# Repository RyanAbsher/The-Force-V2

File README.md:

# The Force V2
 Second version of a show crontroller for The Force Exhibit at the USSRC

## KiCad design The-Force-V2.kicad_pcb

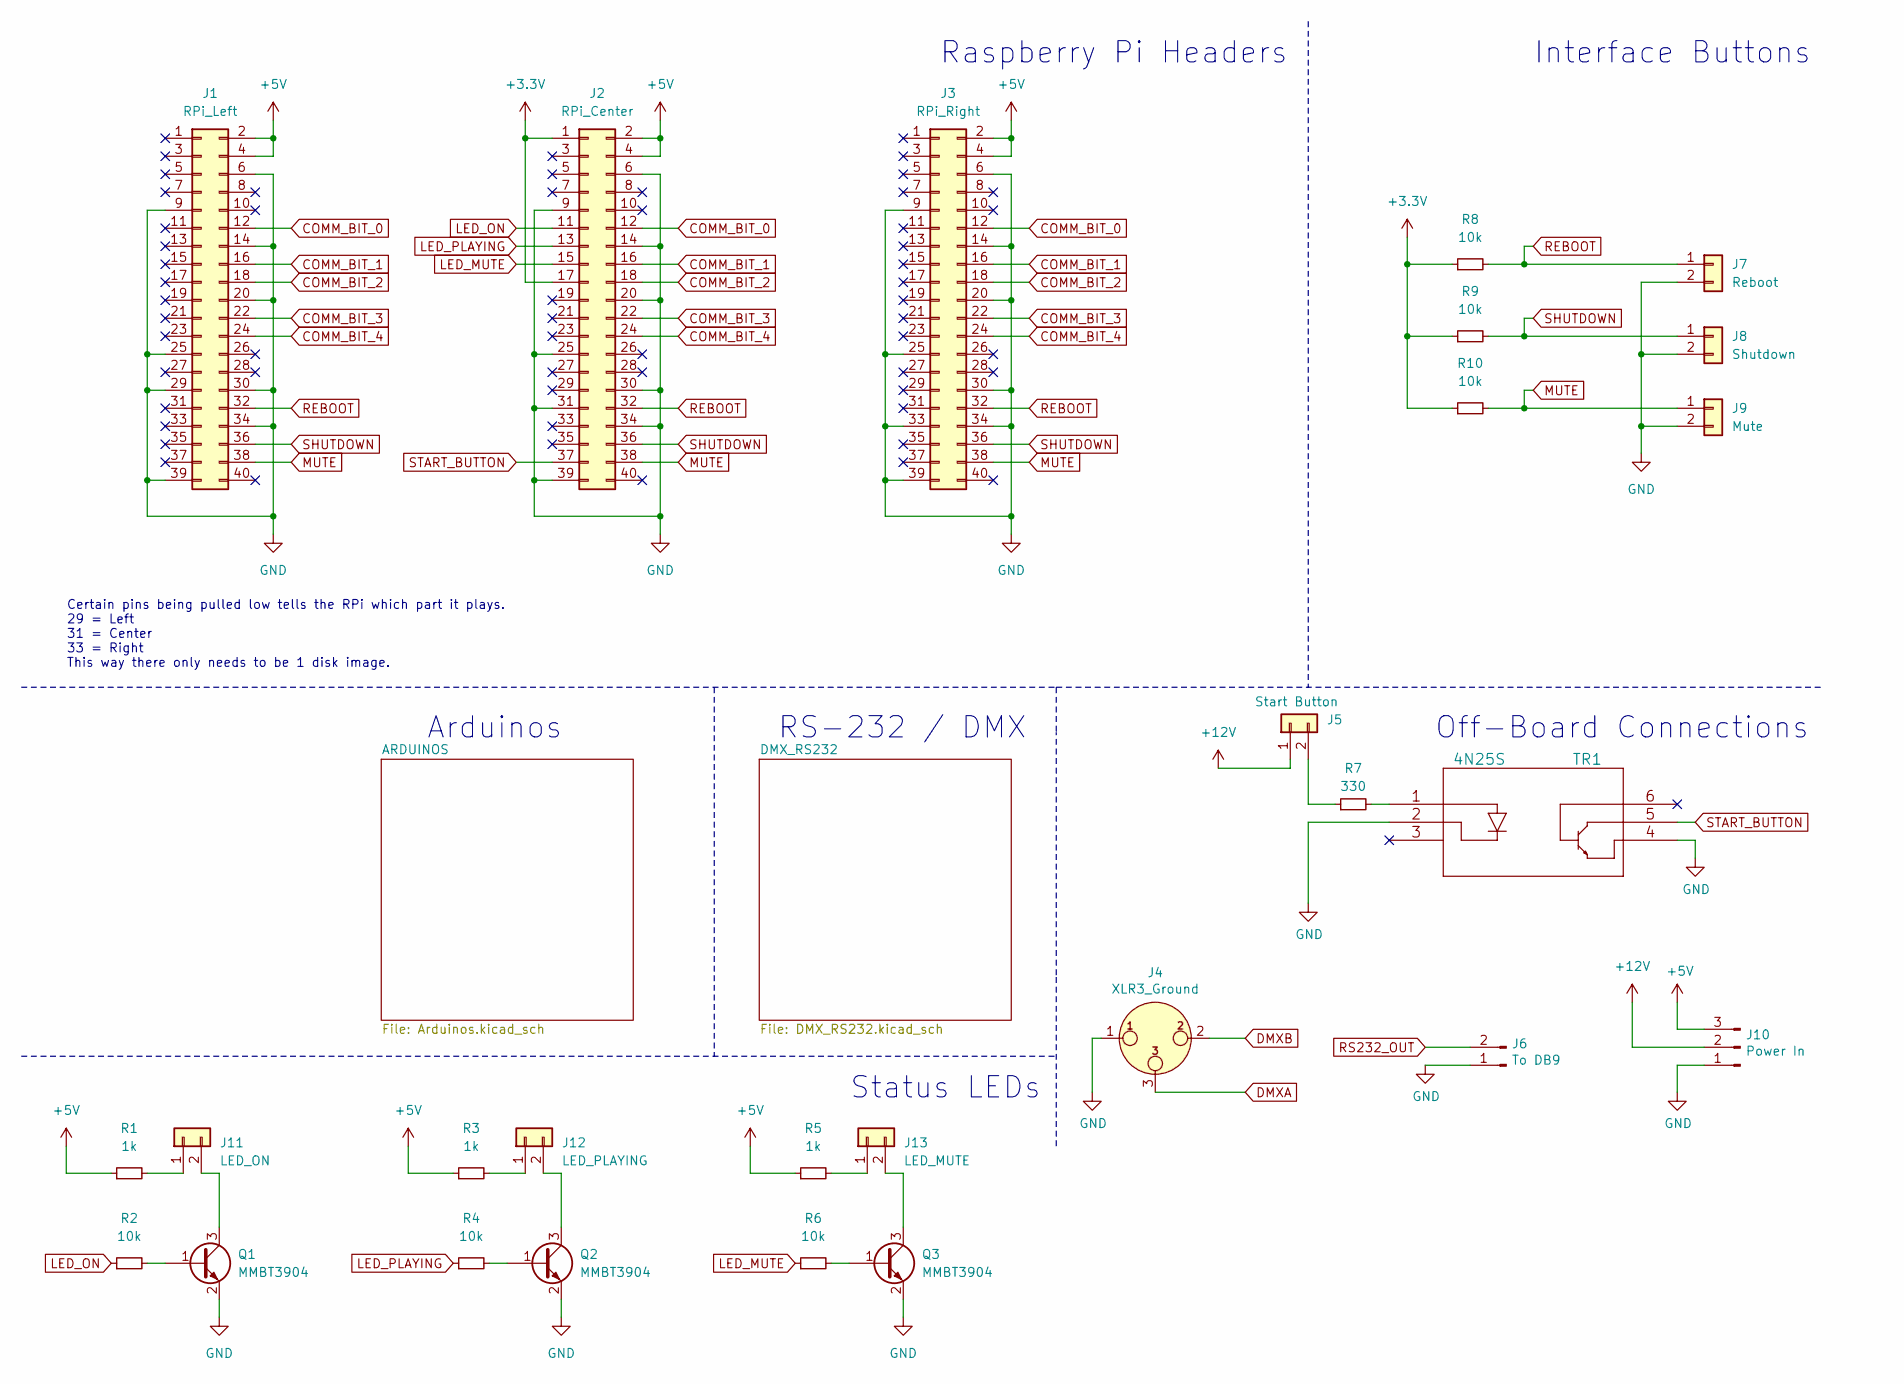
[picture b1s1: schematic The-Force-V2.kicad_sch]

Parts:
J1: RPi_Left; PinHeader_2x20_P2.54mm_Vertical; LCSC Part # C124383
J2: RPi_Center; PinHeader_2x20_P2.54mm_Vertical; LCSC Part # C124383
J3: RPi_Right; PinHeader_2x20_P2.54mm_Vertical; LCSC Part # C124383
J4: XLR3_Ground; PinHeader_1x03_P2.54mm_Vertical; LCSC Part # C49257
J5: Start Button; PinHeader_1x02_P2.54mm_Vertical; LCSC Part # C124375
J6: To DB9; PinHeader_1x02_P2.54mm_Vertical; LCSC Part # C124375
J7: Reboot; PinHeader_1x02_P2.54mm_Vertical; LCSC Part # C124375
J8: Shutdown; PinHeader_1x02_P2.54mm_Vertical; LCSC Part # C124375
J9: Mute; PinHeader_1x02_P2.54mm_Vertical; LCSC Part # C124375
J10: Power In; PinHeader_1x03_P2.54mm_Vertical; LCSC Part # C49257
J11: LED_ON; PinHeader_1x02_P2.54mm_Vertical; LCSC Part # C124375
J12: LED_PLAYING; PinHeader_1x02_P2.54mm_Vertical; LCSC Part # C124375
J13: LED_MUTE; PinHeader_1x02_P2.54mm_Vertical; LCSC Part # C124375
Q1, Q2, Q3: MMBT3904; SOT-23; LCSC Part # C20526
R1, R3, R5: 1k; R_0805_2012Metric_Pad1.20x1.40mm_HandSolder; LCSC Part # C17513
R2, R4, R6, R8, R9, R10: 10k; R_0805_2012Metric_Pad1.20x1.40mm_HandSolder; LCSC Part # C17414
R7: 330; R_0805_2012Metric_Pad1.20x1.40mm_HandSolder; LCSC Part # C17630
TR1: 4N25S; LCSC Part # C143074

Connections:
+3V3: J2.1, J2.17, R8.1, R9.1, R10.1
+5V: J1.2, J1.4, J2.2, J2.4, J3.2, J3.4, J10.3, R1.1, R3.1, R5.1; also elsewhere on the board
+12V: J5.1, J10.2
COMM_BIT_0: J1.12, J2.12, J3.12; also elsewhere on the board
COMM_BIT_1: J1.16, J2.16, J3.16; also elsewhere on the board
COMM_BIT_2: J1.18, J2.18, J3.18; also elsewhere on the board
COMM_BIT_3: J1.22, J2.22, J3.22; also elsewhere on the board
COMM_BIT_4: J1.24, J2.24, J3.24; also elsewhere on the board
DMXA: J4.3; also elsewhere on the board
DMXB: J4.2; also elsewhere on the board
GND: J1.6, J1.9, J1.14, J1.20, J1.25, J1.29, J1.30, J1.34, J1.39, J2.6, J2.9, J2.14, J2.20, J2.25, J2.30, J2.31, J2.34, J2.39, J3.6, J3.9, J3.14, J3.20, J3.25, J3.30, J3.33, J3.34, J3.39, J4.1, J6.1, J7.2, J8.2, J9.2, J10.1, Q1.2 (E), Q2.2 (E), Q3.2 (E), TR1.2, TR1.4; also elsewhere on the board
LED_MUTE: J2.15, R6.1
LED_ON: J2.11, R2.1
LED_PLAYING: J2.13, R4.1
MUTE: J1.38, J2.38, J3.38, J9.1, R10.2
unnamed: J5.2, R7.1
unnamed: J11.1, R1.2
unnamed: J11.2, Q1.3 (C)
unnamed: J12.1, R3.2
unnamed: J12.2, Q2.3 (C)
unnamed: J13.1, R5.2
unnamed: J13.2, Q3.3 (C)
unnamed: Q1.1 (B), R2.2
unnamed: Q2.1 (B), R4.2
unnamed: Q3.1 (B), R6.2
unnamed: R7.2, TR1.1
REBOOT: J1.32, J2.32, J3.32, J7.1, R8.2
RS232_OUT: J6.2; also elsewhere on the board
SHUTDOWN: J1.36, J2.36, J3.36, J8.1, R9.2
START_BUTTON: J2.37, TR1.5

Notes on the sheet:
Status LEDs
Interface Buttons
RS-232 / DMX
Raspberry Pi Headers
Off-Board Connections
Arduinos
Certain pins being pulled low tells the RPi which part it plays. 29 = Left 31 = Center 33 = Right This way there only needs to be 1 disk image.

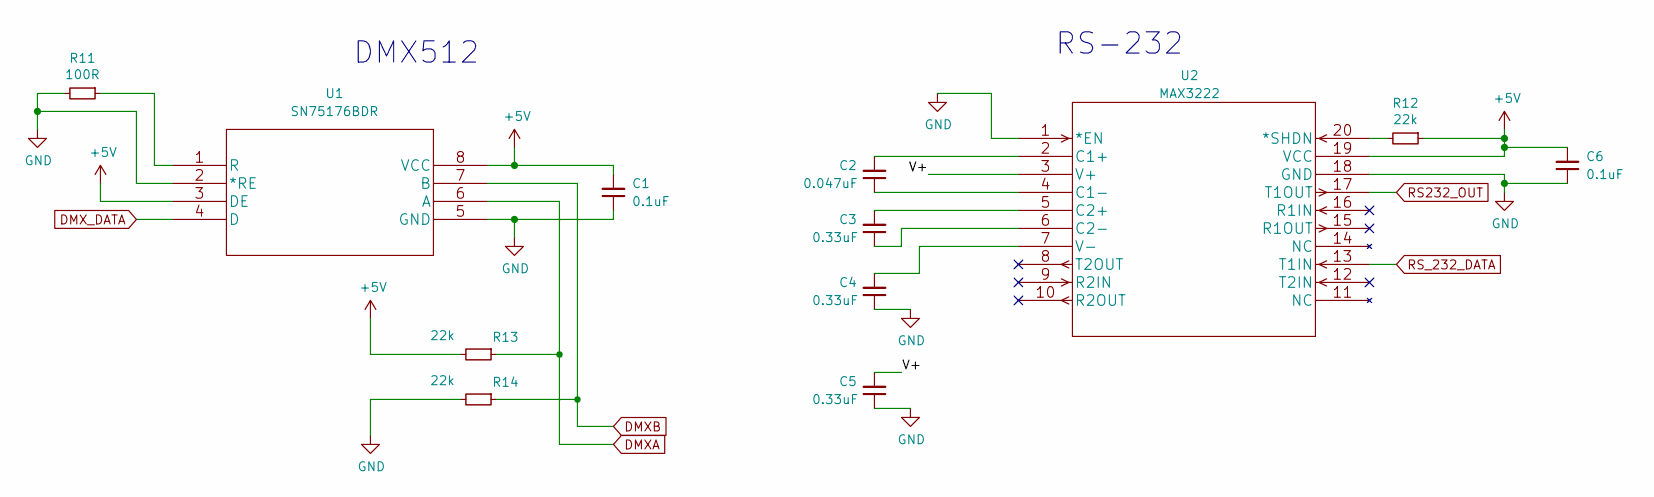
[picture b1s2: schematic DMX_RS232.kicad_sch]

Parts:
C1, C6: 0.1uF; C_0805_2012Metric_Pad1.18x1.45mm_HandSolder; LCSC Part # C49678
C2: 0.047uF; C_0805_2012Metric_Pad1.18x1.45mm_HandSolder; LCSC Part # C53134
C3, C4, C5: 0.33uF; C_0805_2012Metric_Pad1.18x1.45mm_HandSolder; LCSC Part # C1740
R11: 100R; R_0805_2012Metric_Pad1.20x1.40mm_HandSolder; LCSC Part # C17408
R12: 22k; R_0805_2012Metric_Pad1.20x1.40mm_HandSolder; LCSC Part # C17560
R13, R14: 22k; R_0805_2012Metric_Pad1.20x1.40mm_HandSolder; LCSC Part # C17414
U1: SN75176BDR; SOIC-8_3.9x4.9mm_P1.27mm; LCSC Part # C7063
U2: MAX3222; TSSOP-20_4.4x6.5mm_P0.65mm; LCSC Part # C124672

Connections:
+5V: C1.2, C6.2, R12.1, R13.2, U1.3 (DE), U1.8 (VCC), U2.19 (VCC); also elsewhere on the board
/DMX_RS232/V+: C5.2, U2.3 (V+)
DMXA: R13.1, U1.6 (A); also elsewhere on the board
DMXB: R14.1, U1.7 (B); also elsewhere on the board
DMX_DATA: U1.4 (D); also elsewhere on the board
GND: C1.1, C4.1, C5.1, C6.1, R11.2, R14.2, U1.2 (*RE), U1.5 (GND), U2.1 (*EN), U2.18 (GND); also elsewhere on the board
unnamed: C2.1, U2.4 (C1-)
unnamed: C2.2, U2.2 (C1+)
unnamed: C3.1, U2.6 (C2-)
unnamed: C3.2, U2.5 (C2+)
unnamed: C4.2, U2.7 (V-)
unnamed: R11.1, U1.1 (R)
unnamed: R12.2, U2.20 (*SHDN)
RS232_OUT: U2.17 (T1OUT); also elsewhere on the board
RS_232_DATA: U2.13 (T1IN); also elsewhere on the board

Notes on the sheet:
DMX512
RS-232

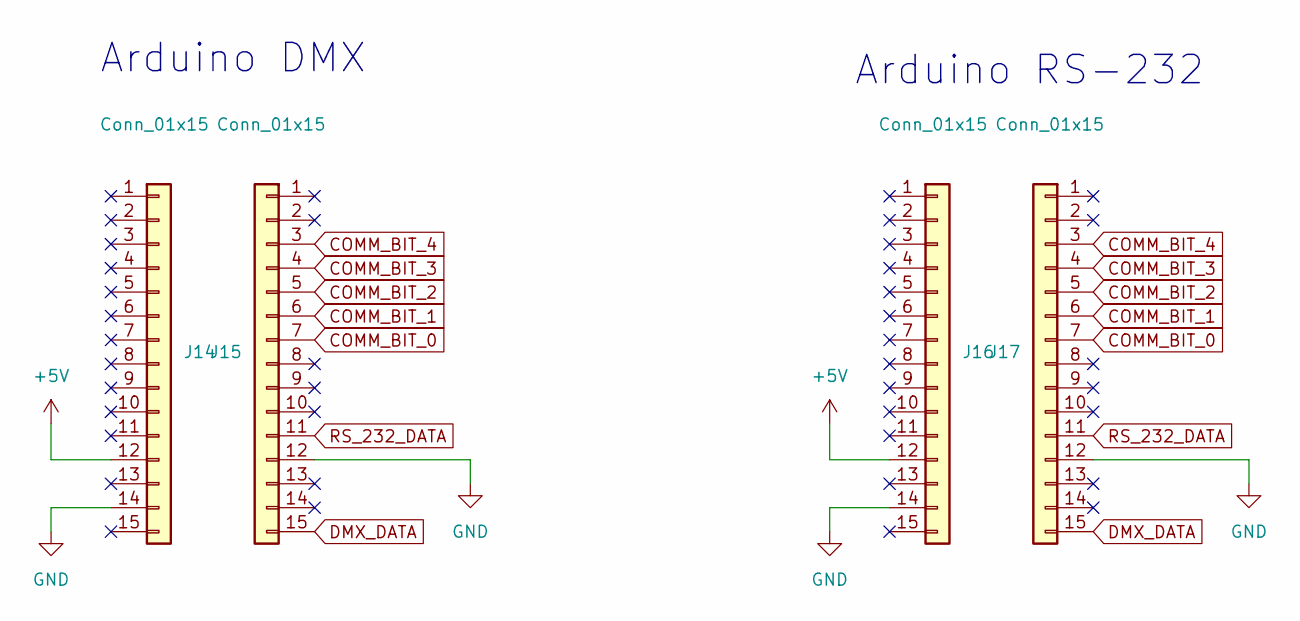
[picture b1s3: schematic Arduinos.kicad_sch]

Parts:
J14, J15, J16, J17: Conn_01x15; PinSocket_1x15_P2.54mm_Vertical; LCSC C124408

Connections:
+5V: J14.12, J16.12; also elsewhere on the board
COMM_BIT_0: J15.7, J17.7; also elsewhere on the board
COMM_BIT_1: J15.6, J17.6; also elsewhere on the board
COMM_BIT_2: J15.5, J17.5; also elsewhere on the board
COMM_BIT_3: J15.4, J17.4; also elsewhere on the board
COMM_BIT_4: J15.3, J17.3; also elsewhere on the board
DMX_DATA: J15.15, J17.15; also elsewhere on the board
GND: J14.14, J15.12, J16.14, J17.12; also elsewhere on the board
RS_232_DATA: J15.11, J17.11; also elsewhere on the board

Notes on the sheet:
Arduino RS-232
Arduino DMX

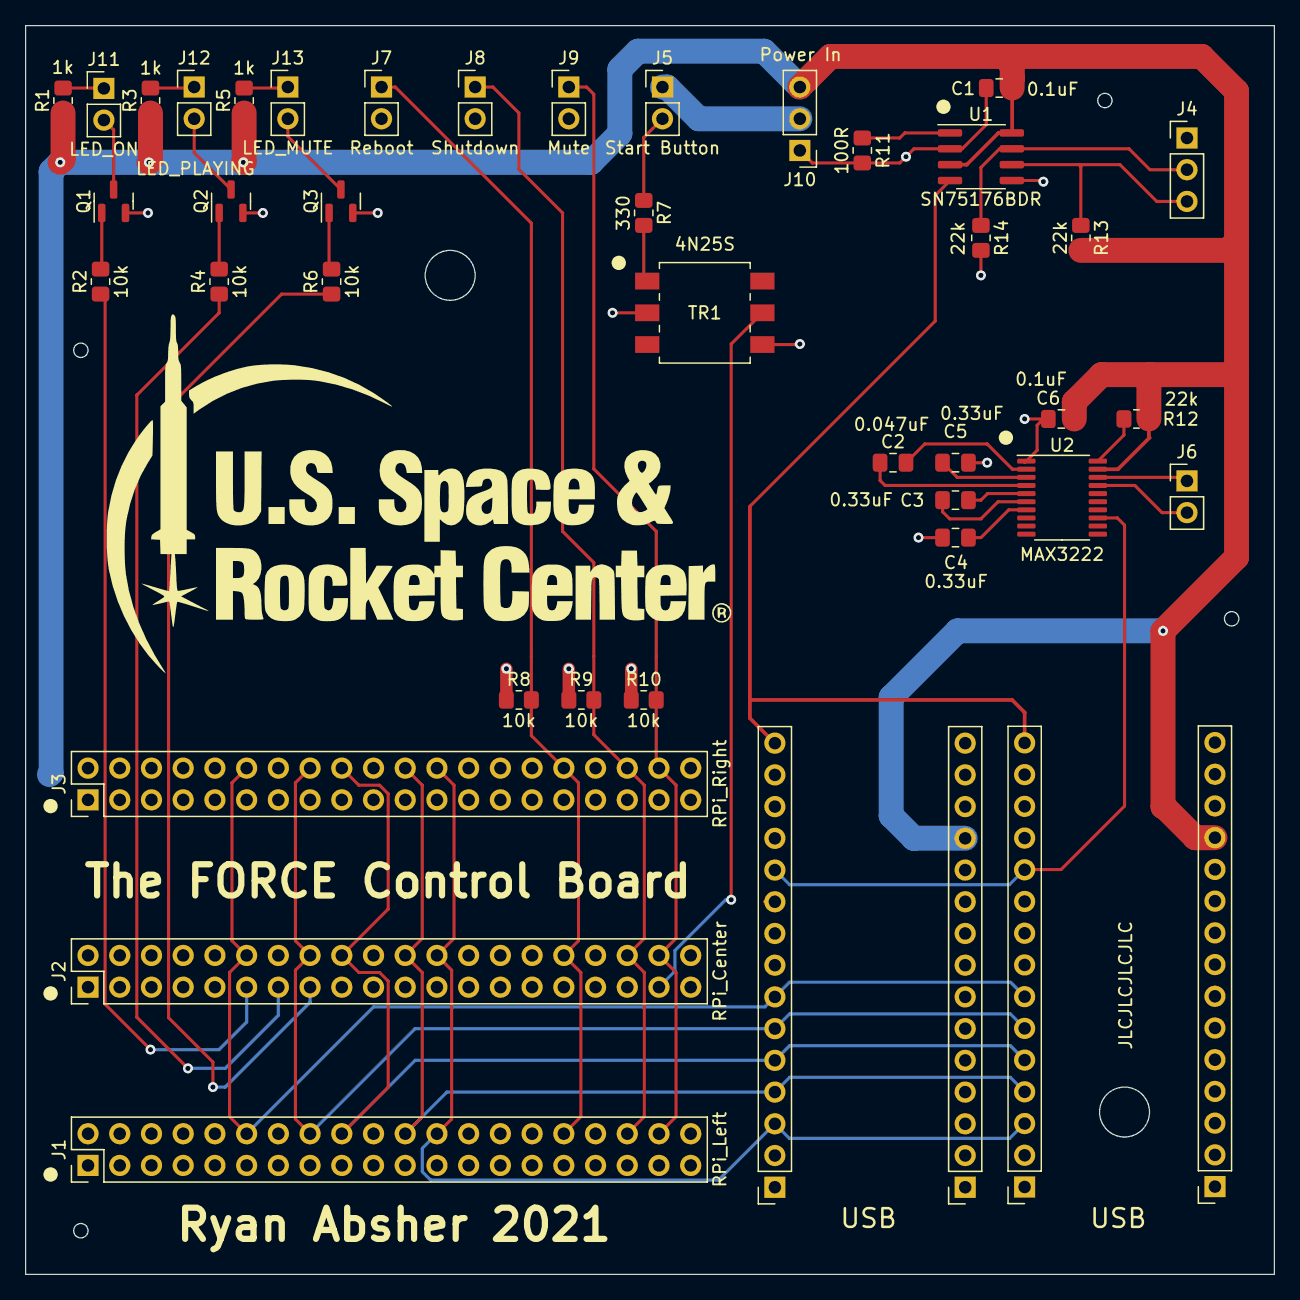
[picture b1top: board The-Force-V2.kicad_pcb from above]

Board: 4 copper layers, 100.0 x 100.0 mm, 43 parts (0 on the bottom side), 40 nets.

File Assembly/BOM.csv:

Comment,Designator,Footprint,LCSC
0.1uF,"C1,C6",Capacitor_SMD:C_0805_2012Metric_Pad1.18x1.45mm_HandSolder,C49678
0.047uF,C2,Capacitor_SMD:C_0805_2012Metric_Pad1.18x1.45mm_HandSolder,C53134
0.33uF,"C3,C4,C5",Capacitor_SMD:C_0805_2012Metric_Pad1.18x1.45mm_HandSolder,C1740
MMBT3904,"Q1,Q2,Q3",Package_TO_SOT_SMD:SOT-23,C20526
1k,"R1,R3,R5",Resistor_SMD:R_0805_2012Metric_Pad1.20x1.40mm_HandSolder,C17513
100R,R11,Resistor_SMD:R_0805_2012Metric_Pad1.20x1.40mm_HandSolder,C17408
22k,"R12,R13,R14",Resistor_SMD:R_0805_2012Metric_Pad1.20x1.40mm_HandSolder,C17560
10k,"R2,R4,R6,R8,R9,R10",Resistor_SMD:R_0805_2012Metric_Pad1.20x1.40mm_HandSolder,C17414
330R,R7,Resistor_SMD:R_0805_2012Metric_Pad1.20x1.40mm_HandSolder,C17630
4N25S,TR1,footprints:4N25S,C143074
SN75176BDR,U1,Package_SO:SOIC-8_3.9x4.9mm_P1.27mm,C7063
MAX3222,U2,Package_SO:TSSOP-20_4.4x6.5mm_P0.65mm,C124672

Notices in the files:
parts and their libraries:
Copyright 2021 Accelerated Designs. All rights reserved.
